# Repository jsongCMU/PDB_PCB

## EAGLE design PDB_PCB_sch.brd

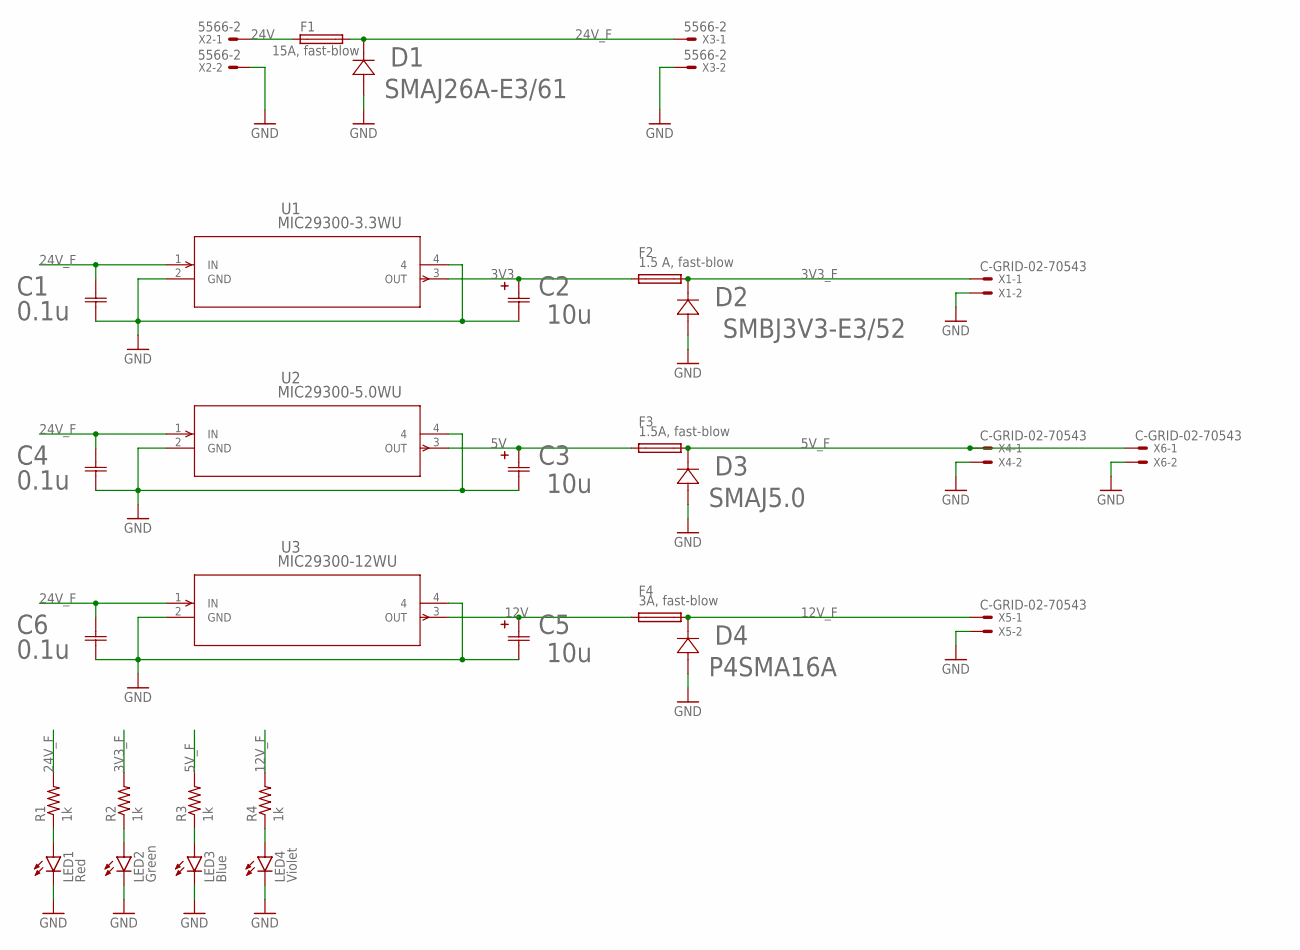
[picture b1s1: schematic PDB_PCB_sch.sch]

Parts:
C1, C4, C6: 0.1u; CAP_0402_WAL
C2, C3, C5: 10u; CAP_TCS_M_ROM
D1: SMAJ26A-E3/61; DIODE_DO-214AC
D2: SMBJ3V3-E3/52; DO-214AC_VIS
D3: SMAJ5.0; SMASERIES_LTF
D4: P4SMA16A; P4SMASERIES_LTF
F1: 15A, fast-blow; TE5
F2: 1.5 A, fast-blow; TE5
F3: 1.5A, fast-blow; TE5
F4: 3A, fast-blow; TE5
LED1: Red; 1206
LED2: Green; 1206
LED3: Blue; 1206
LED4: Violet; 1206
R1, R2, R3, R4: 1k; R0402
U1: MIC29300-3.3WU; TO-263-3_MCL
U2: MIC29300-5.0WU; TO-263-3_MCL
U3: MIC29300-12WU; TO-263-3_MCL
X1, X4, X5, X6: C-GRID-02-70543; 70543-02
X2, X3: 5566-2

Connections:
3V3: C2.2, F2.1, U1.3 (OUT)
3V3_F: D2.11, F2.2, R2.2, X1.1
5V: C3.2, F3.1, U2.3 (OUT)
5V_F: D3.1 (11), F3.2, R3.2, X4.1, X6.1
12V: C5.2, F4.1, U3.3 (OUT)
12V_F: D4.1 (11), F4.2, R4.2, X5.1
24V: F1.1, X2.1
24V_F: C1.1, C4.1, C6.1, R1.2, U1.1 (IN), U2.1 (IN), U3.1 (IN)
GND: C1.2, C2.1, C3.1, C4.2, C5.1, C6.2, D1.2 (12), D2.12, D3.2 (12), D4.2 (12), LED1.C, LED2.C, LED3.C, LED4.C, U1.2 (GND), U1.4, U2.2 (GND), U2.4, U3.2 (GND), U3.4, X1.2, X2.2, X3.2, X4.2, X5.2, X6.2
unnamed: LED1.A, R1.1
unnamed: LED2.A, R2.1
unnamed: LED3.A, R3.1
unnamed: D1.1 (11), F1.2, X3.1
unnamed: LED4.A, R4.1

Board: 2 copper layers, 31 parts (0 on the bottom side), 14 nets, no tracks yet.

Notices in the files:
parts and their libraries:
COPYRIGHT: Copyright (C) 2022 Ultra Librarian. All rights reserved.
